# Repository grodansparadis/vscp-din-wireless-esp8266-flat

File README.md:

# vscp-din-wireless-esp8266-flat
ESP8266 based VSCP controller in flat DIN package. The usage for the modul is to interface a P1 electricity meter and report meter readings over VSCP.

Can be powered from the meter or externally.

**Note!** This is still a prototype.

## PCB's

---

Part of the [VSCP Project](https://www.vscp.org).

Copyright 2021-2022 © Åke Hedman, (Grodans Paradis AB)[https://www.grodansparadis.com]

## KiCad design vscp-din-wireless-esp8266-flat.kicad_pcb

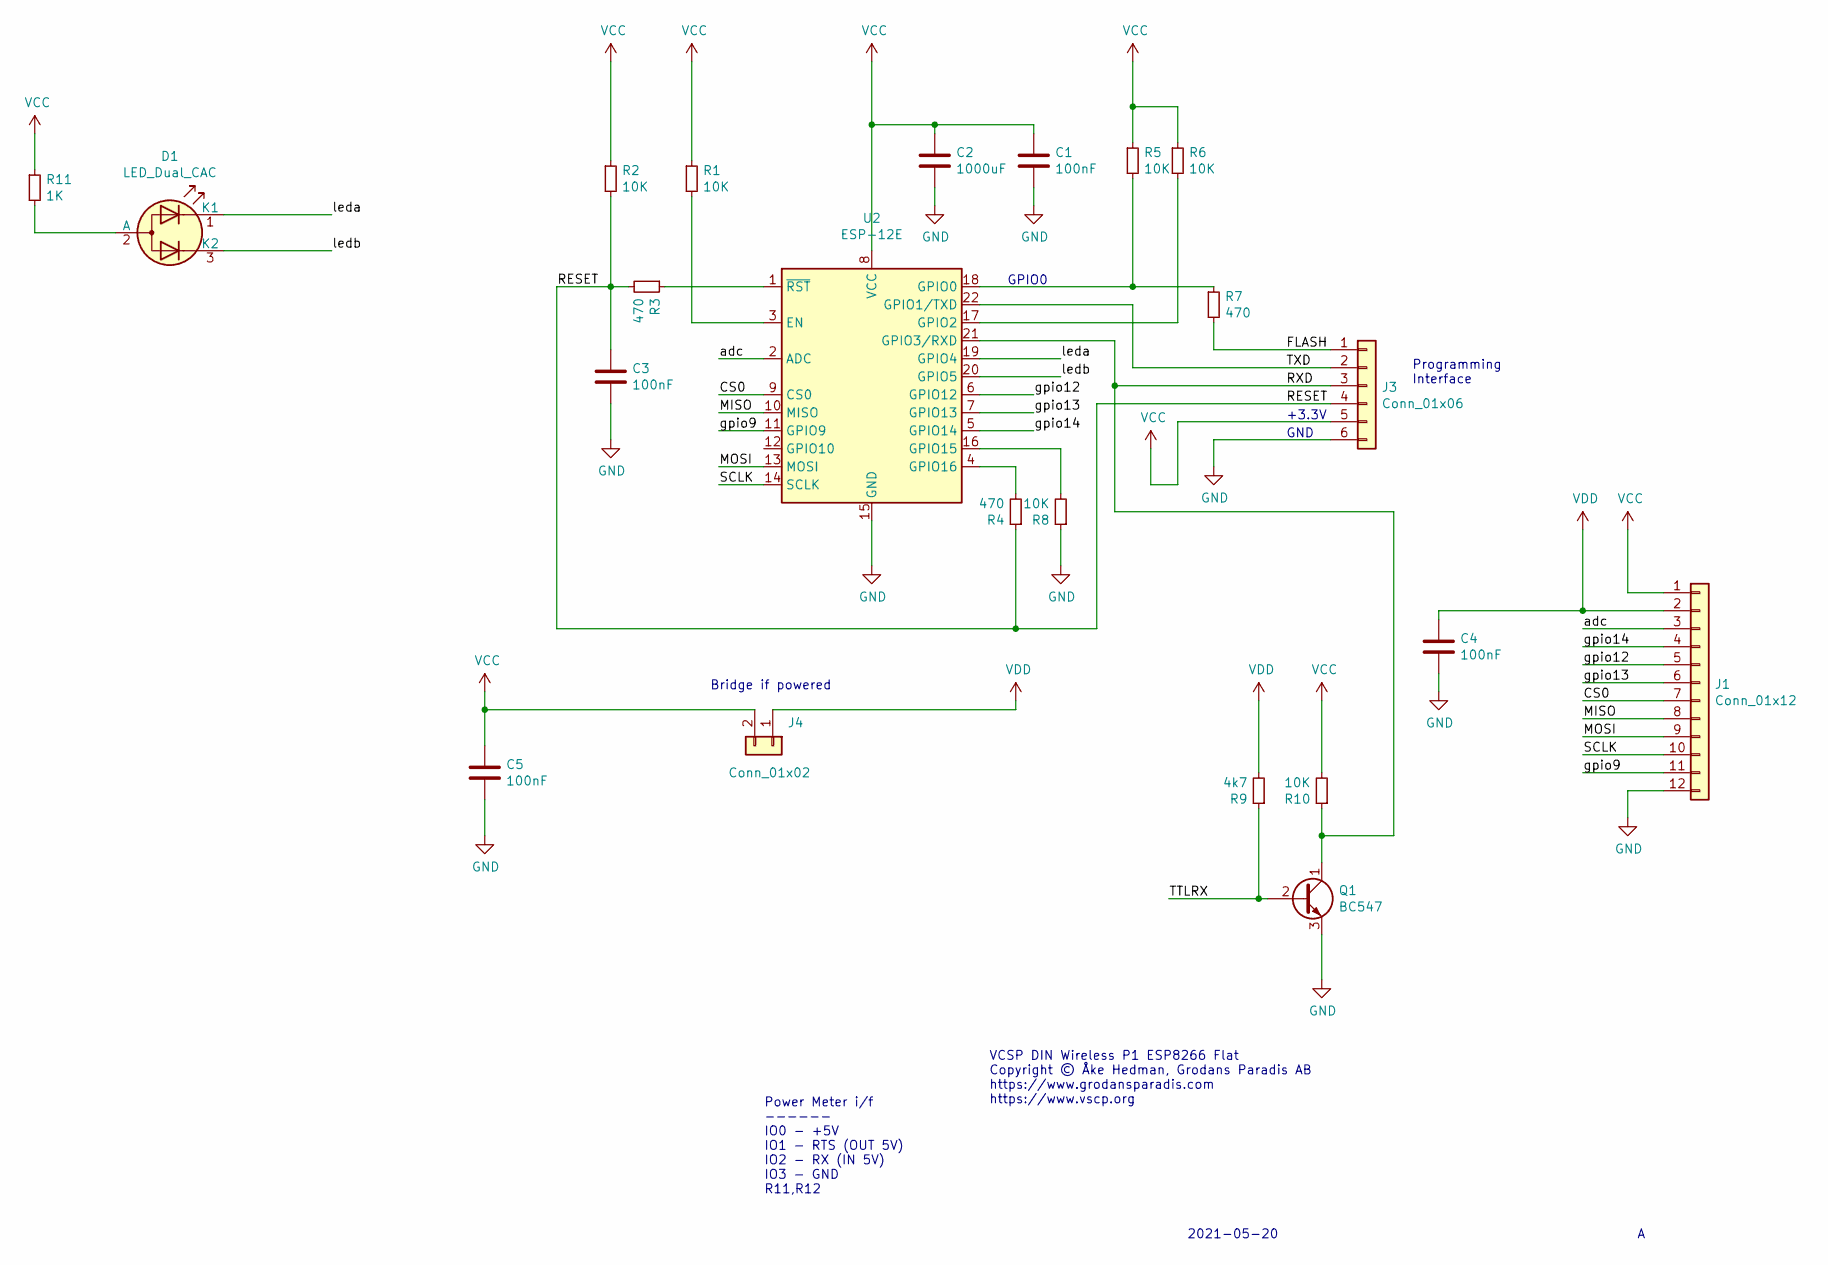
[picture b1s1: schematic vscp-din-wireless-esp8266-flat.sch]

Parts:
C1, C3, C4, C5: 100nF; C_0805_2012Metric
C2: 1000uF; CP_Radial_D5.0mm_P2.50mm
D1: LED_Dual_CAC; LED_D5.0mm-3
J1: Conn_01x12; PinSocket_1x12_P2.54mm_Vertical
J3: Conn_01x06; PinHeader_1x06_P2.54mm_Vertical
J4: Conn_01x02; PinHeader_1x02_P2.54mm_Vertical
Q1: BC547; TO-92_Inline
R1, R2, R5, R6, R8, R10: 10K; R_0805_2012Metric
R3, R7: 470; R_0805_2012Metric
R4: 470; C_0805_2012Metric
R9: 4k7; R_0805_2012Metric
R11: 1K; R_0805_2012Metric
U2: ESP-12E

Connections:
/CS0: J1.7, U2.9 (CS0)
/FLASH: J3.1, R7.2
/MISO: J1.8, U2.10 (MISO)
/MOSI: J1.9, U2.13 (MOSI)
/RESET: C3.1, J3.4, R2.2, R3.2, R4.1
/RXD: J3.3, Q1.1 (C), R10.1, U2.21 (GPIO3/RXD)
/SCLK: J1.10, U2.14 (SCLK)
/TTLRX: Q1.2 (B), R9.1
/TXD: J3.2, U2.22 (GPIO1/TXD)
/adc: J1.3, U2.2 (ADC)
/gpio9: J1.11, U2.11 (GPIO9)
/gpio12: J1.5, U2.6 (GPIO12)
/gpio13: J1.6, U2.7 (GPIO13)
/gpio14: J1.4, U2.5 (GPIO14)
/leda: D1.1 (K1), U2.19 (GPIO4)
/ledb: D1.3 (K2), U2.20 (GPIO5)
GND: C1.2, C2.2, C3.2, C4.2, C5.2, J1.12, J3.6, Q1.3 (E), R8.1, U2.15 (GND); also elsewhere on the board
unnamed: D1.2 (A), R11.2
unnamed: R1.2, U2.3 (EN)
unnamed: R3.1, U2.1 (~RST)
unnamed: R4.2, U2.4 (GPIO16)
unnamed: R5.2, R7.1, U2.18 (GPIO0)
unnamed: R6.2, U2.17 (GPIO2)
unnamed: R8.2, U2.16 (GPIO15)
VCC: C1.1, C2.1, C5.1, J1.1, J3.5, J4.2, R1.1, R2.1, R5.1, R6.1, R10.2, R11.1, U2.8 (VCC)
VDD: C4.1, J1.2, J4.1, R9.2; also elsewhere on the board

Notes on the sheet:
VCSP DIN Wireless P1 ESP8266 Flat Copyright © Åke Hedman, Grodans Paradis AB https://www.grodansparadis.com https://www.vscp.org
2021-05-20
GND
Programming Interface
+3.3V
Power Meter i/f ------ IO0 - +5V IO1 - RTS (OUT 5V) IO2 - RX (IN 5V) IO3 - GND R11,R12
GPIO0
Bridge if powered

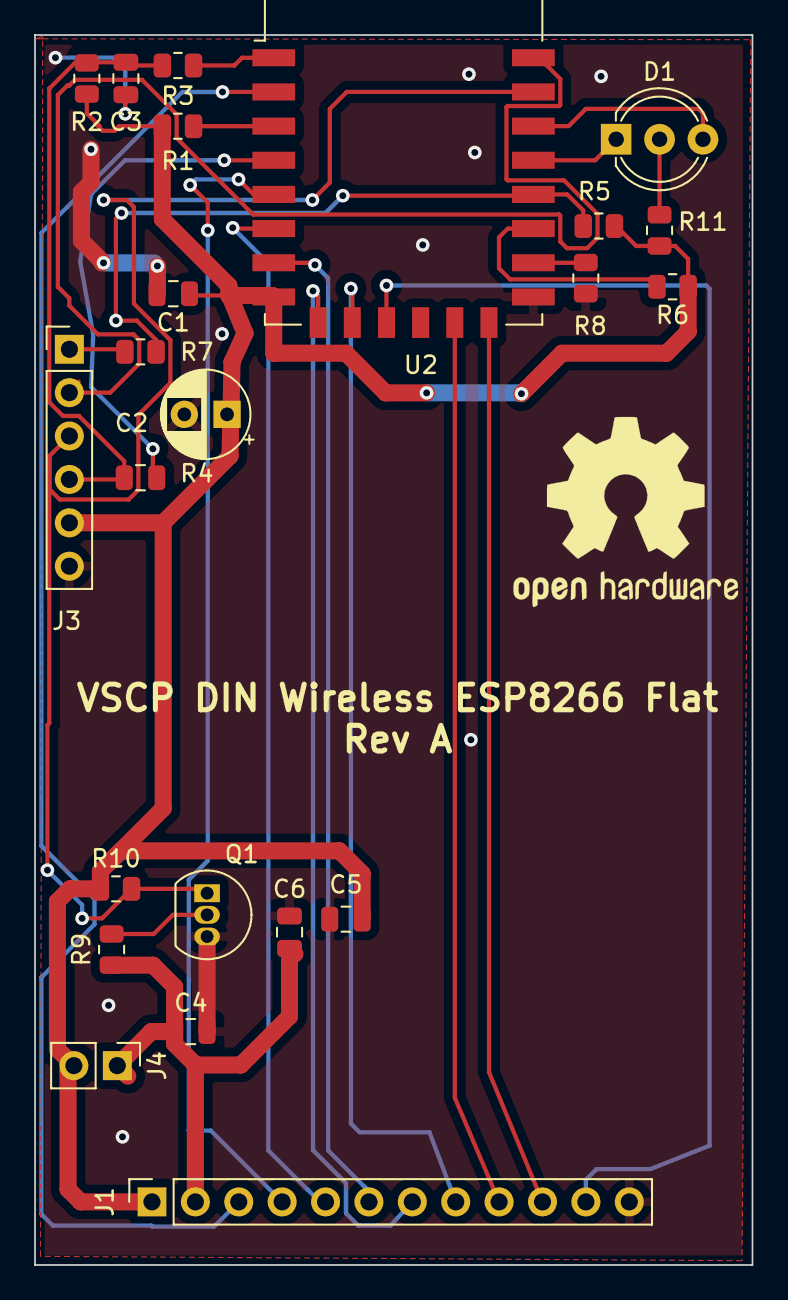
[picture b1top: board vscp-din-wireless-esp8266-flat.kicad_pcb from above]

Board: 2 copper layers, 42.0 x 72.0 mm, 23 parts (0 on the bottom side), 26 nets.

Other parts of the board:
C6: 100nF; C_0805_2012Metric

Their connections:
GND: C6.2; also elsewhere on the board
VDD: C6.1; also elsewhere on the board

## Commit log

2021-05-24 Initial import
2021-05-25 Removed obsolite file
2021-05-25 Added gerbers
2021-05-25 Added initial info
2022-02-03 Updated copyright
